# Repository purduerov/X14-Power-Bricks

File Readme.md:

# Readme for X14-Power-Bricks

Whenever you make a new part, download the datasheet and save it here _**and**_ with the part in the parts library

Always pull other people's changes before beginning to work
`git pull`

Be sure to push your changes after  working on them. Run:
1. `git add .` to add any files in this directory or a subdirectory
or `git add -u` to add any modified files
2. (Optional) `git clean -nX` to see what ignored files can be removed
	`git clean -fX` removes ignored files (Eagle backups)
3. `git commit -m "helpful commit message"` with a description of the work that you did
4. `git push` to push your work to github

Other helpful commands
* `git status` says information about modified and staged files
* `git log` shows the recent commits of the repository
* `git log filename.extension` show the recent commits for just that file
* `git checkout first-couple-letter-of-commit-id` lets you go back to a previous version
* `git checkout master` brings you back to the latest commit
* `git tag` lists the tags
* `git tag -a orderX -m "the version of the board placed for the X'th order"` tag a specific commit
* `git push --tags` needed to push tags to remote
* `git show orderX` show the commit log for the given tag
* `git checkout orderX` go back and interact with the files at the tagged commit

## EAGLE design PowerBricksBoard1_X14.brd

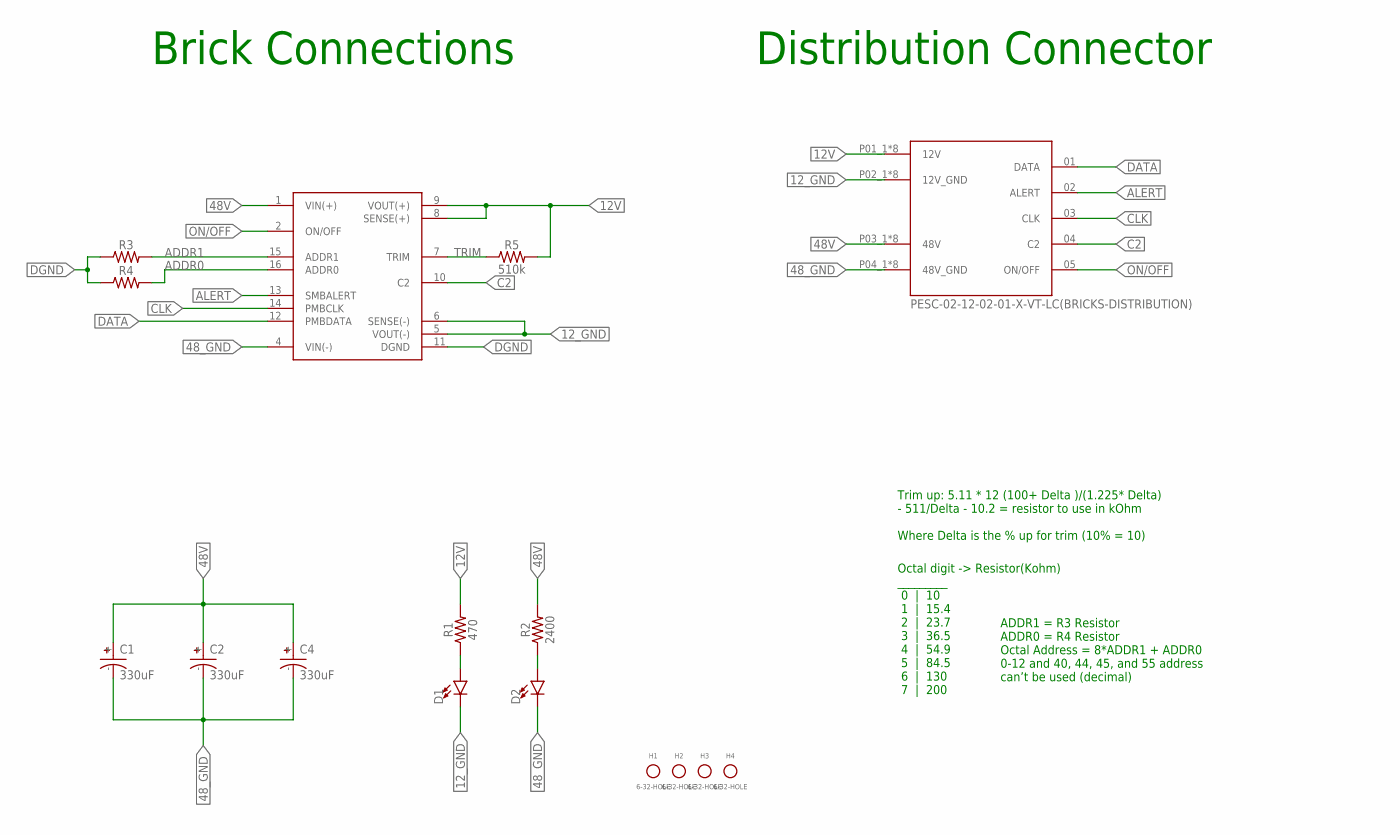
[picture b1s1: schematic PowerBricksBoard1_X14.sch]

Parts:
C1, C2, C4: 330uF; CAPAE1030X1050N
D1, D2: LED0603; LED-0603
H1, H2, H3, H4: 6-32-HOLE
J1: PESC-02-12-02-01-X-VT-LC(BRICKS-DISTRIBUTION); SAMTEC_PESC-02-12-02-01-X-VT-LC(B-D)
R1: 470; 0603
R2: 2400; 0603
R3, R4: 0603
R5: 510k; 0603
U$2: Q48SC12050NRDH

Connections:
12V: J1.P01_1 (12V), J1.P01_2 (12V), J1.P01_3 (12V), J1.P01_4 (12V), J1.P01_5 (12V), J1.P01_6 (12V), J1.P01_7 (12V), J1.P01_8 (12V), R1.2, R5.2, U$2.8 (SENSE(+)), U$2.9 (VOUT(+))
12_GND: D1.C, J1.P02_1 (12V_GND), J1.P02_2 (12V_GND), J1.P02_3 (12V_GND), J1.P02_4 (12V_GND), J1.P02_5 (12V_GND), J1.P02_6 (12V_GND), J1.P02_7 (12V_GND), J1.P02_8 (12V_GND), U$2.5 (VOUT(-)), U$2.6 (SENSE(-))
48V: C1.+, C2.+, C4.+, J1.P03_1 (48V), J1.P03_2 (48V), J1.P03_3 (48V), J1.P03_4 (48V), J1.P03_5 (48V), J1.P03_6 (48V), J1.P03_7 (48V), J1.P03_8 (48V), R2.2, U$2.1 (VIN(+))
48_GND: C1.-, C2.-, C4.-, D2.C, J1.P04_1 (48V_GND), J1.P04_2 (48V_GND), J1.P04_3 (48V_GND), J1.P04_4 (48V_GND), J1.P04_5 (48V_GND), J1.P04_6 (48V_GND), J1.P04_7 (48V_GND), J1.P04_8 (48V_GND), U$2.4 (VIN(-))
ADDR0: R4.2, U$2.16 (ADDR0)
ADDR1: R3.2, U$2.15 (ADDR1)
ALERT: J1.02 (ALERT), U$2.13 (SMBALERT)
C2: J1.04 (C2), U$2.10 (C2)
CLK: J1.03 (CLK), U$2.14 (PMBCLK)
DATA: J1.01 (DATA), U$2.12 (PMBDATA)
DGND: R3.1, R4.1, U$2.11 (DGND)
unnamed: D1.A, R1.1
unnamed: D2.A, R2.1
ON/OFF: J1.05 (ON/OFF), U$2.2 (ON/OFF)
TRIM: R5.1, U$2.7 (TRIM)

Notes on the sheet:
Octal digit -> Resistor(Kohm) _________ 0 | 10 1 | 15.4 2 | 23.7 3 | 36.5 4 | 54.9 5 | 84.5 6 | 130 7 | 200
ADDR1 = R3 Resistor ADDR0 = R4 Resistor Octal Address = 8*ADDR1 + ADDR0 0-12 and 40, 44, 45, and 55 address can’t be used (decimal)
Brick Connections
Distribution Connector
Trim up: 5.11 * 12 (100+ Delta )/(1.225* Delta) - 511/Delta - 10.2 = resistor to use in kOhm Where Delta is the % up for trim (10% = 10)

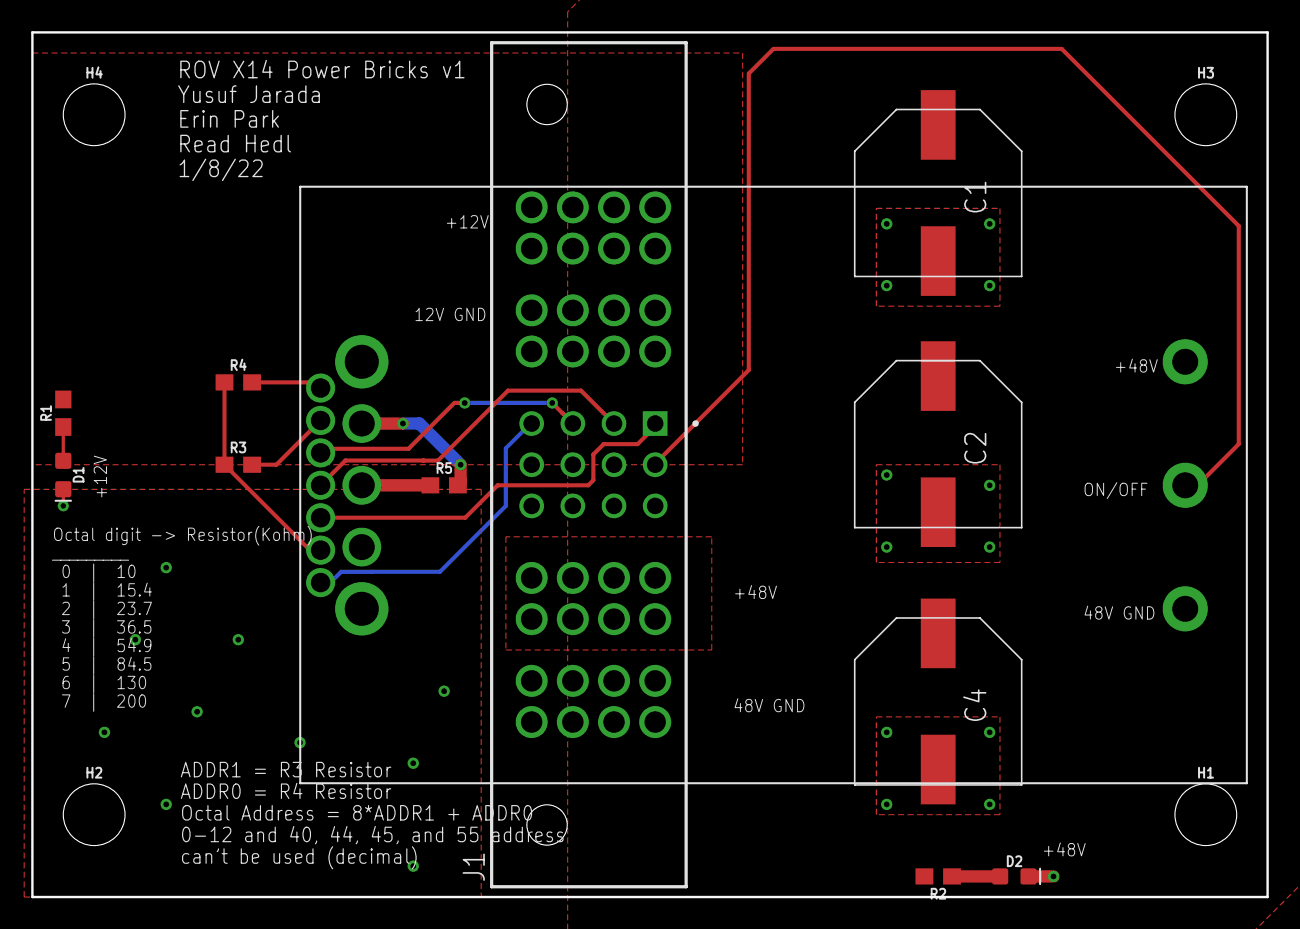
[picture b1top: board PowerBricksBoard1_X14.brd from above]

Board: 2 copper layers, 76.2 x 53.3 mm, 16 parts (0 on the bottom side), 15 nets.

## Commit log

2021-09-18 readme+gitignore
2021-10-02 changed name
2021-10-20 imported new connector into drawing
2021-10-30 Board Size
2021-11-20 I deleted the old board and made a new one with the connector type.
2021-11-27 adjusted board size
2021-11-29 Needed a design review and some bugs
    DRC keepings giving me polygon priority issues
2021-12-04 update
    erin plz help
2021-12-04 Fixed things
2021-12-04 final
2021-12-09 dsss
2021-12-11 update - erin plz look at
2021-12-30 more adjustments
2021-12-30 fixed an issue
2022-01-02 Final Touches
    I implemented the final design suggestions, sorry it was so late
2022-01-07 Added Silkscreen
2022-04-09 changed the hole with the new connector
2022-04-16 Update from documentation

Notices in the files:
parts and their libraries:
SparkFun-LED: Licensing: Creative Commons ShareAlike 4.0 International - https://creativecommons.org/licenses/by-sa/4.0
